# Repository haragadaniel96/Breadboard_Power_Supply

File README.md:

# Breadboard_Power_Supply

**Project Overview:**
Designed and developed a versatile linear power supply module tailored for rapid electronic prototyping and breadboard environments. The system takes a 12V DC input and provides two fully independent, jumper-selectable output channels delivering stable 5V and 3.3V power rails.

**Hardware Architecture & Schematic Design:**
* **Power Input Stage:** Integrated a 12V DC Barrel Jack equipped with a main power switch for safe operation, alongside a dedicated LED power-presence indicator with a calculated current-limiting resistor.
* **Fixed Voltage Stage (5V):** Implemented an LM7805 linear voltage regulator to establish a constant 5V power rail. Included standard decoupling capacitors to filter high-frequency noise and ensure stability.
* **Adjustable Voltage Stage (3.3V):** Configured an LM317 adjustable linear regulator to generate a stable 3.3V rail. Accurately calculated and implemented a resistive voltage divider to set the reference voltage, paired with a 1µF output capacitor for optimal transient response.

**User-Centric Design & Connectivity:**
* **Independent Channel Selection:** Engineered an output architecture featuring two isolated delivery channels. Integrated 3-pin header selectors that allow the user to independently route either the 5V or 3.3V rail to each specific output.
* **Dual-Interface Outputs:** Maximized benchtop versatility by providing two physical connection methods per channel: standard 2.54mm pin headers (optimized for Dupont wires and direct breadboard insertion) and screw terminals for secure, high-current bare-wire connections.

### Schematic

### Design PCB 

### 3D View

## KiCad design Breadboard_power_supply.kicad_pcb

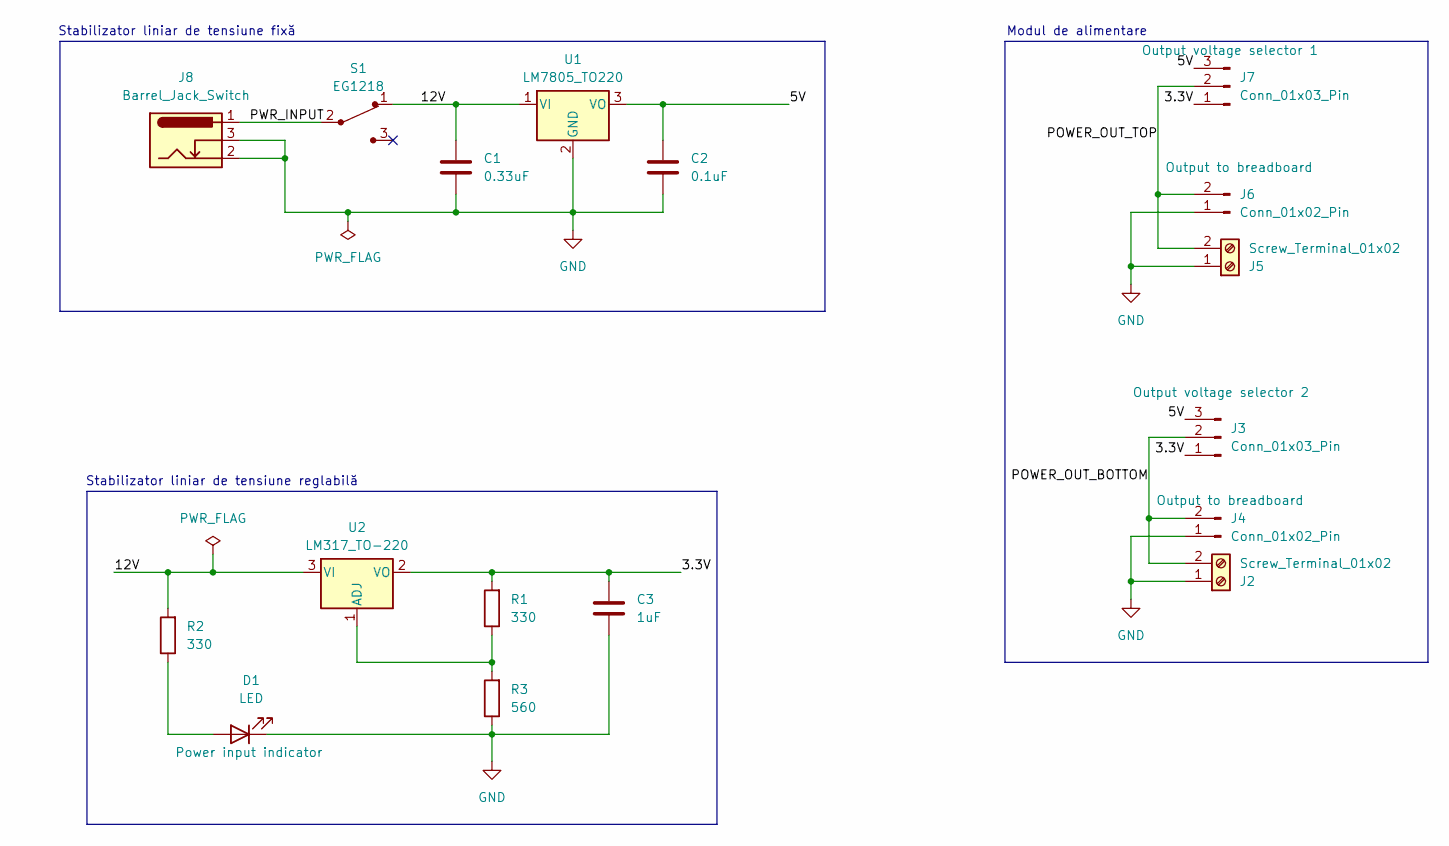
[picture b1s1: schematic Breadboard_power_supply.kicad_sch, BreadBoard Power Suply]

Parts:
C1: 0.33uF; C_Disc_D3.0mm_W1.6mm_P2.50mm
C2: 0.1uF; C_Disc_D3.0mm_W1.6mm_P2.50mm
C3: 1uF; C_Disc_D3.0mm_W1.6mm_P2.50mm
D1: LED; LED_D5.0mm
J2, J5: Screw_Terminal_01x02; TerminalBlock_MaiXu_MX126-5.0-02P_1x02_P5.00mm
J3, J7: Conn_01x03_Pin; PinHeader_1x03_P2.54mm_Vertical
J4, J6: Conn_01x02_Pin; PinHeader_1x02_P2.54mm_Vertical
J8: Barrel_Jack_Switch; BarrelJack_Horizontal
R1, R2: 330; R_Axial_DIN0207_L6.3mm_D2.5mm_P7.62mm_Horizontal
R3: 560; R_Axial_DIN0207_L6.3mm_D2.5mm_P7.62mm_Horizontal
S1: EG1218; Switch_Slide_11.6x4mm_EG1218; MPN EG1218; Digi-Key_PN EG1903-ND
U1: LM7805_TO220; TO-220-3_Vertical
U2: LM317_TO-220; TO-220-3_Vertical

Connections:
/3.3V: C3.1, J3.1, J7.1, R1.2, U2.2 (VO)
/5V: C2.1, J3.3, J7.3, U1.3 (VO)
/12V: C1.1, R2.2, S1.1, U1.1 (VI), U2.3 (VI)
/POWER_OUT_BOTTOM: J2.2, J3.2, J4.2
/POWER_OUT_TOP: J5.2, J6.2, J7.2
/PWR_INPUT: J8.1, S1.2
GND: C1.2, C2.2, C3.2, D1.1 (K), J2.1, J4.1, J5.1, J6.1, J8.2, J8.3, R3.1, U1.2 (GND)
unnamed: D1.2 (A), R2.1
unnamed: R1.1, R3.2, U2.1 (ADJ)

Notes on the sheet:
Modul de alimentare
Stabilizator liniar de tensiune fixă
Stabilizator liniar de tensiune reglabilă

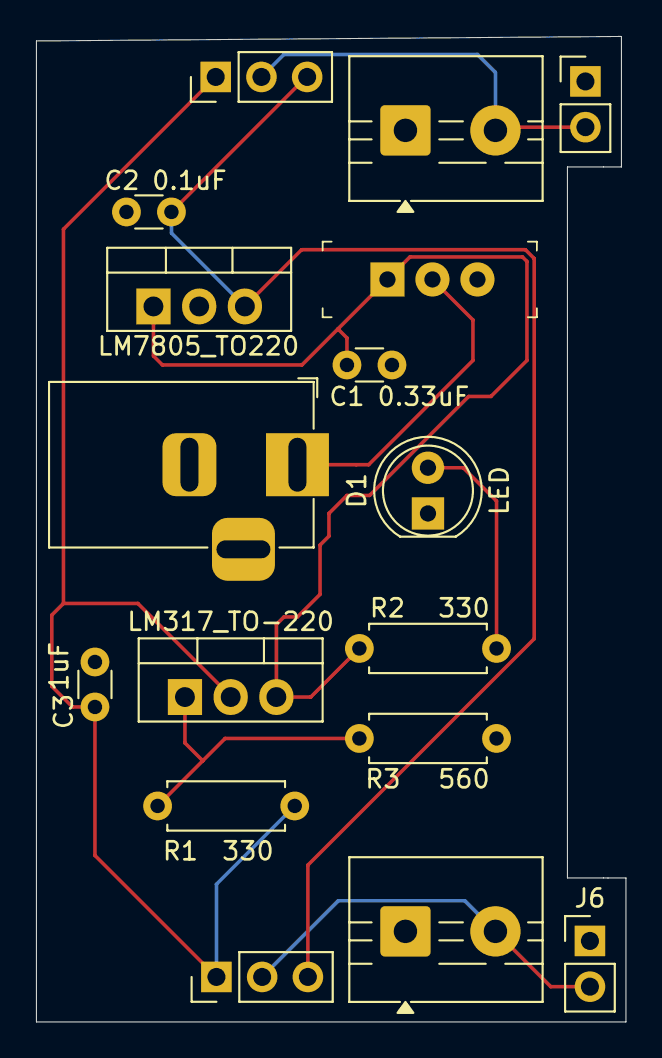
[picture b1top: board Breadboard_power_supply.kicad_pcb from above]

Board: 2 copper layers, 32.8 x 54.8 mm, 17 parts (0 on the bottom side), 9 nets.

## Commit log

2026-03-05 README.md
